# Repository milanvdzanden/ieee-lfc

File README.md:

# IEEE Line Follower Competition
This repository will serve as the main source of all technical details related to the Line Follower Competition. This repository also contains all design files for the robot template kit, which will be made available for purchase as well. Some example code will be provided but you are completely free to change these design files, code and even the robot to get an edge over the other teams.

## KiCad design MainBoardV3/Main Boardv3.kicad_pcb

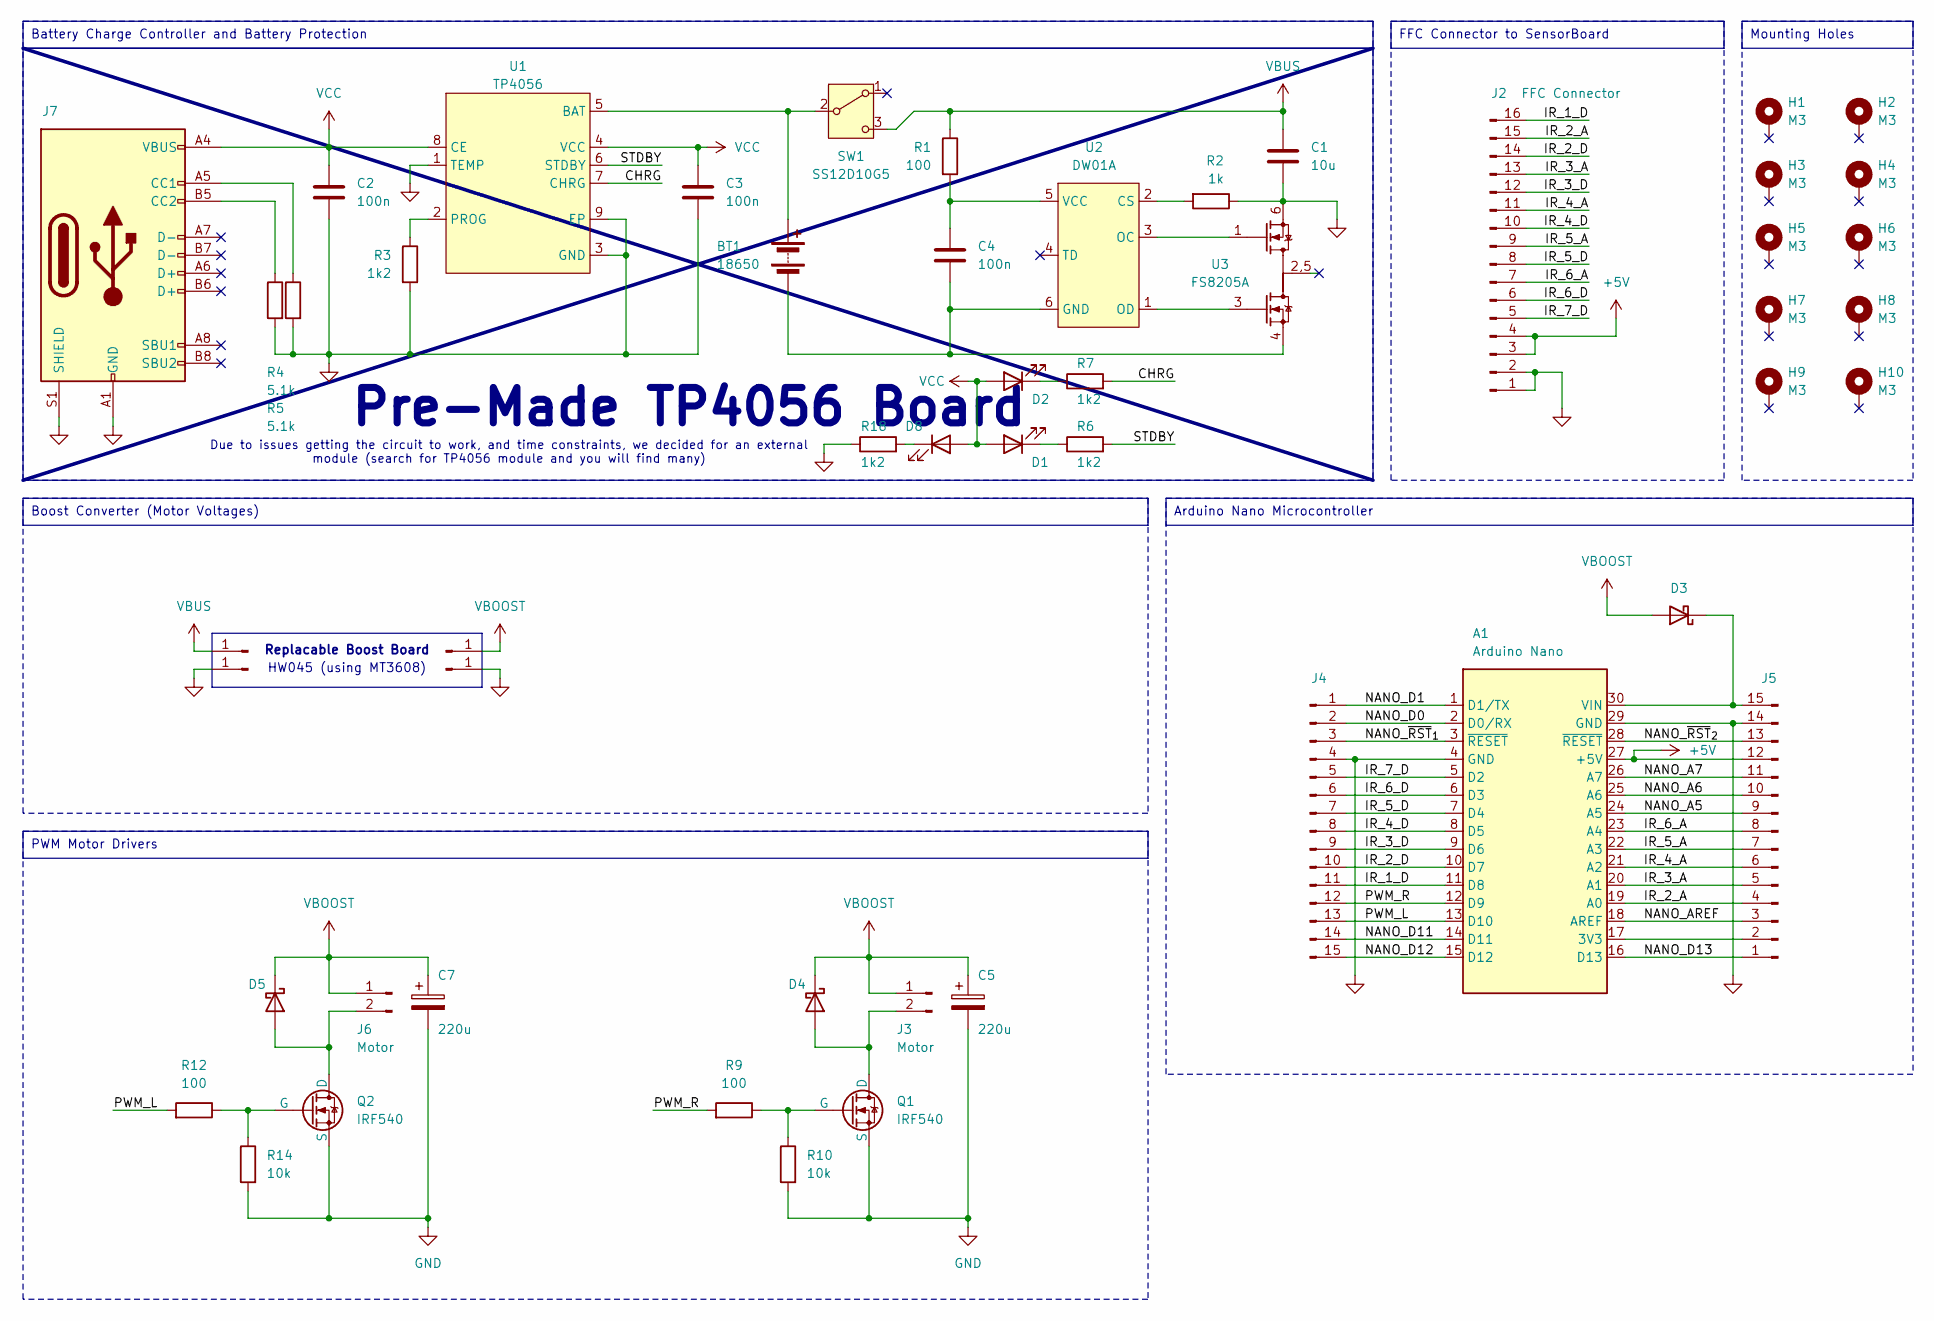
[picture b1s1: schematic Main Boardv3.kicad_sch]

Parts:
A1: Arduino Nano; Arduino_Nano
BT1: 18650; BatteryHolder_Keystone_1042_1x18650
C1: 10u; C_0603_1608Metric
C2, C3, C4: 100n; C_0603_1608Metric
C5, C7: 220u; CP_Radial_D8.0mm_P5.00mm
D1, D2, D8: LED; LED_0603_1608Metric
D3, D4, D5: D_Schottky; D_SMA
H1, H2, H3, H4, H5, H6, H7, H8, H9, H10: M3; MountingHole_Soldernut_M3
J2: FFC Connector; Hirose_FH12-16S-0.5SH_1x16-1MP_P0.50mm_Horizontal
J3, J6: Motor; TerminalBlock_bornier-2_P5.08mm
J4, J5: Row 2; PinSocket_1x15_P2.54mm_Vertical
J7: USB_C_Receptacle_USB2.0_16P; USB_C_Receptacle_GCT_USB4105-xx-A_16P_TopMnt_Horizontal
J101, J102, J103, J104: Conn_01x01_Pin; PinHeader_1x01_P2.54mm_Vertical
Q1, Q2: IRF540; TO-220F-3_Vertical
R1, R9, R12: 100; R_0603_1608Metric
R2: 1k; R_0603_1608Metric
R3, R6, R7, R18: 1k2; R_0603_1608Metric
R4, R5: 5.1k; R_0603_1608Metric
R10, R14: 10k; R_0603_1608Metric
SW1: SS12D10G5; SS12D10G5_SlideSwitch
U1: TP4056; Infineon_PG-DSO-8-27_3.9x4.9mm_EP2.65x3mm
U2: DW01A; SOT-23-6
U3: FS8205A; SOT-23-6

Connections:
+5V: A1.27 (+5V), J2.3, J2.4, J5.12
/CHRG: R7.2, U1.7 (CHRG)
/IR_1_D: A1.11 (D8), J2.16, J4.11
/IR_2_A: A1.19 (A0), J2.15, J5.4
/IR_2_D: A1.10 (D7), J2.14, J4.10
/IR_3_A: A1.20 (A1), J2.13, J5.5
/IR_3_D: A1.9 (D6), J2.12, J4.9
/IR_4_A: A1.21 (A2), J2.11, J5.6
/IR_4_D: A1.8 (D5), J2.10, J4.8
/IR_5_A: A1.22 (A3), J2.9, J5.7
/IR_5_D: A1.7 (D4), J2.8, J4.7
/IR_6_A: A1.23 (A4), J2.7, J5.8
/IR_6_D: A1.6 (D3), J2.6, J4.6
/IR_7_D: A1.5 (D2), J2.5, J4.5
/NANO_A5: A1.24 (A5), J5.9
/NANO_A6: A1.25 (A6), J5.10
/NANO_A7: A1.26 (A7), J5.11
/NANO_AREF: A1.18 (AREF), J5.3
/NANO_D0: A1.2 (D0/RX), J4.2
/NANO_D1: A1.1 (D1/TX), J4.1
/NANO_D11: A1.14 (D11), J4.14
/NANO_D12: A1.15 (D12), J4.15
/NANO_D13: A1.16 (D13), J5.1
/NANO_~RST_{1}: A1.3 (~RESET), J4.3
/NANO_~RST_{2}: A1.28 (~RESET), J5.13
/PWM_L: A1.13 (D10), J4.13, R12.2
/PWM_R: A1.12 (D9), J4.12, R9.2
/STDBY: R6.2, U1.6 (STDBY)
GND: A1.4 (GND), A1.29 (GND), C1.2, C2.2, C3.2, C5.2, C7.2, J2.1, J2.2, J4.4, J5.14, J7.A1 (GND), J7.A12 (GND), J7.B1 (GND), J7.B12 (GND), J7.S1 (SHIELD), J102.1, J104.1, Q1.3 (S), Q2.3 (S), R2.1, R3.2, R4.2, R5.2, R10.2, R14.2, R18.1, U1.1 (TEMP), U1.3 (GND), U1.9 (EP), U3.6
unnamed: A1.17 (3V3), J5.2
unnamed: A1.30 (VIN), D3.1 (K), J5.15
unnamed: BT1.1 (+), SW1.2 (B), U1.5 (BAT)
unnamed: BT1.2 (-), C4.2, U2.6 (GND), U3.4
unnamed: D1.1 (K), R6.1
unnamed: D2.1 (K), R7.1
unnamed: D4.2 (A), J3.2, Q1.2 (D)
unnamed: D5.2 (A), J6.2, Q2.2 (D)
unnamed: D8.1 (K), R18.2
unnamed: J7.A5 (CC1), R5.1
unnamed: J7.B5 (CC2), R4.1
unnamed: Q1.1 (G), R9.1, R10.1
unnamed: Q2.1 (G), R12.1, R14.1
unnamed: R3.1, U1.2 (PROG)
unnamed: R2.2, U2.2 (CS)
unnamed: U2.3 (OC), U3.1
unnamed: U2.1 (OD), U3.3
unnamed: C4.1, R1.2, U2.5 (VCC)
VBOOST: C5.1, C7.1, D3.2 (A), D4.1 (K), D5.1 (K), J3.1, J6.1, J103.1
VBUS: C1.1, J101.1, R1.1, SW1.3 (C)
VCC: C2.1, C3.1, D1.2 (A), D2.2 (A), D8.2 (A), J7.A4 (VBUS), J7.A9 (VBUS), J7.B4 (VBUS), J7.B9 (VBUS), U1.4 (VCC), U1.8 (CE)

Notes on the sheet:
Mounting Holes
Arduino Nano Microcontroller
Battery Charge Controller and Battery Protection
FFC Connector to SensorBoard
Boost Converter (Motor Voltages)
PWM Motor Drivers
HW045 (using MT3608)
Replacable Boost Board
Due to issues getting the circuit to work, and time constraints, we decided for an external module (search for TP4056 module and you will find many)
Pre-Made TP4056 Board

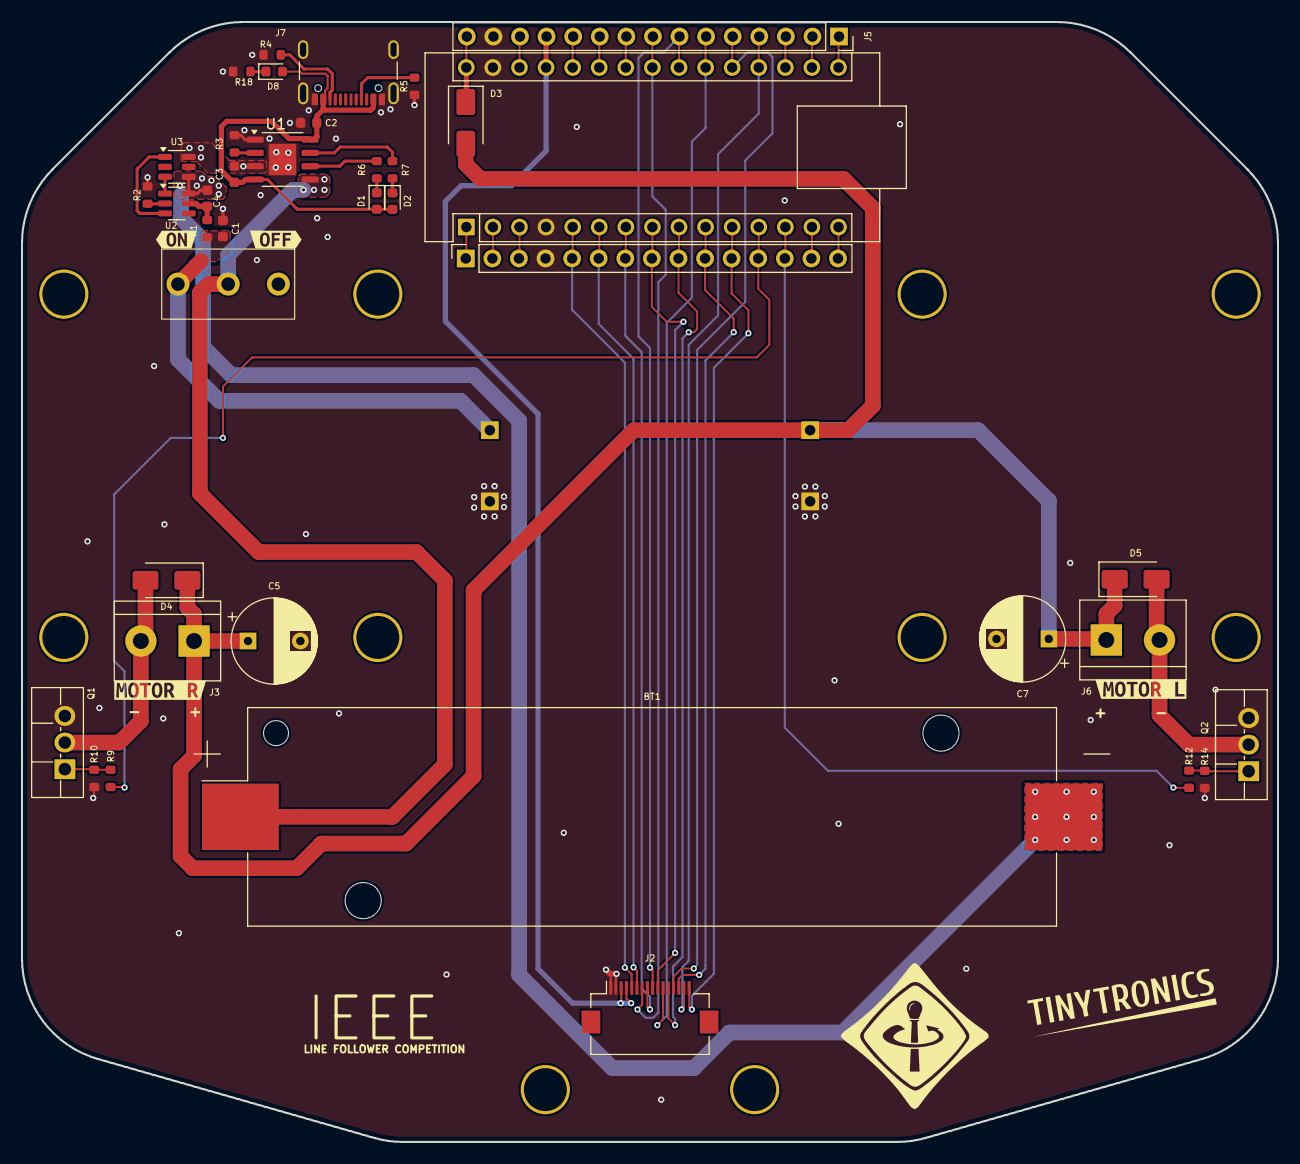
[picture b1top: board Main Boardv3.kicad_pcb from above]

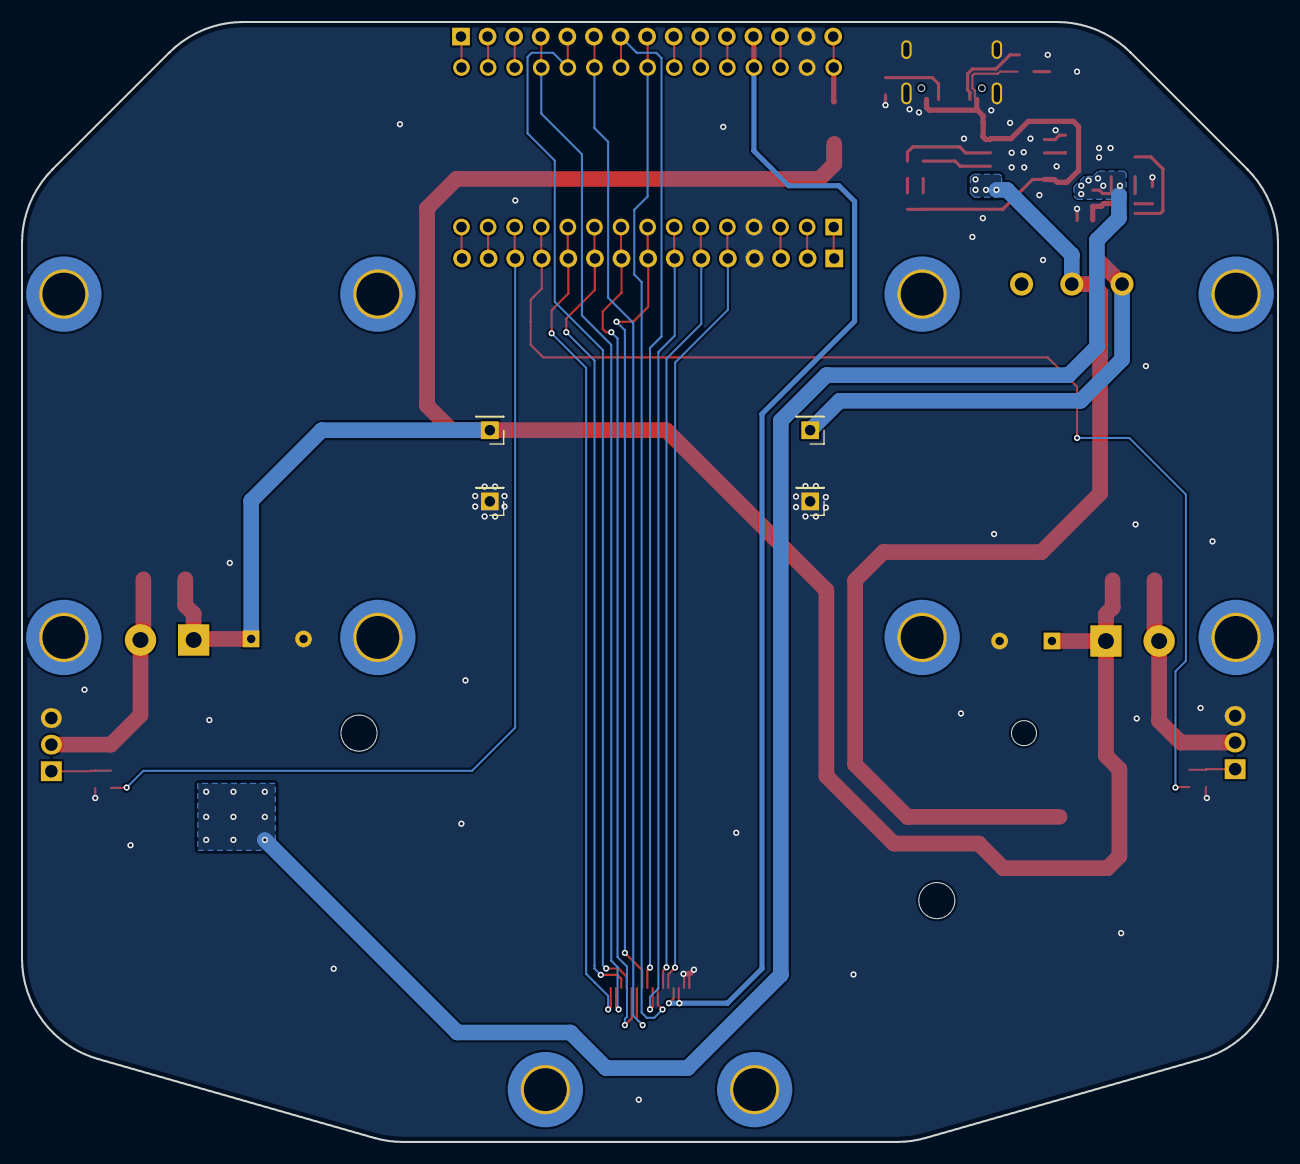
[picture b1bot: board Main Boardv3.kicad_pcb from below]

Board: 2 copper layers, 120.0 x 107.0 mm, 56 parts (14 on the bottom side), 50 nets.

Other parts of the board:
kibuzzard-666C7E6A: G***; kibuzzard-666C7E6A
kibuzzard-666C7E77: G***; kibuzzard-666C7E77
kibuzzard-666C76A4: G***; kibuzzard-666C76A4
kibuzzard-666C76B2: G***; kibuzzard-666C76B2

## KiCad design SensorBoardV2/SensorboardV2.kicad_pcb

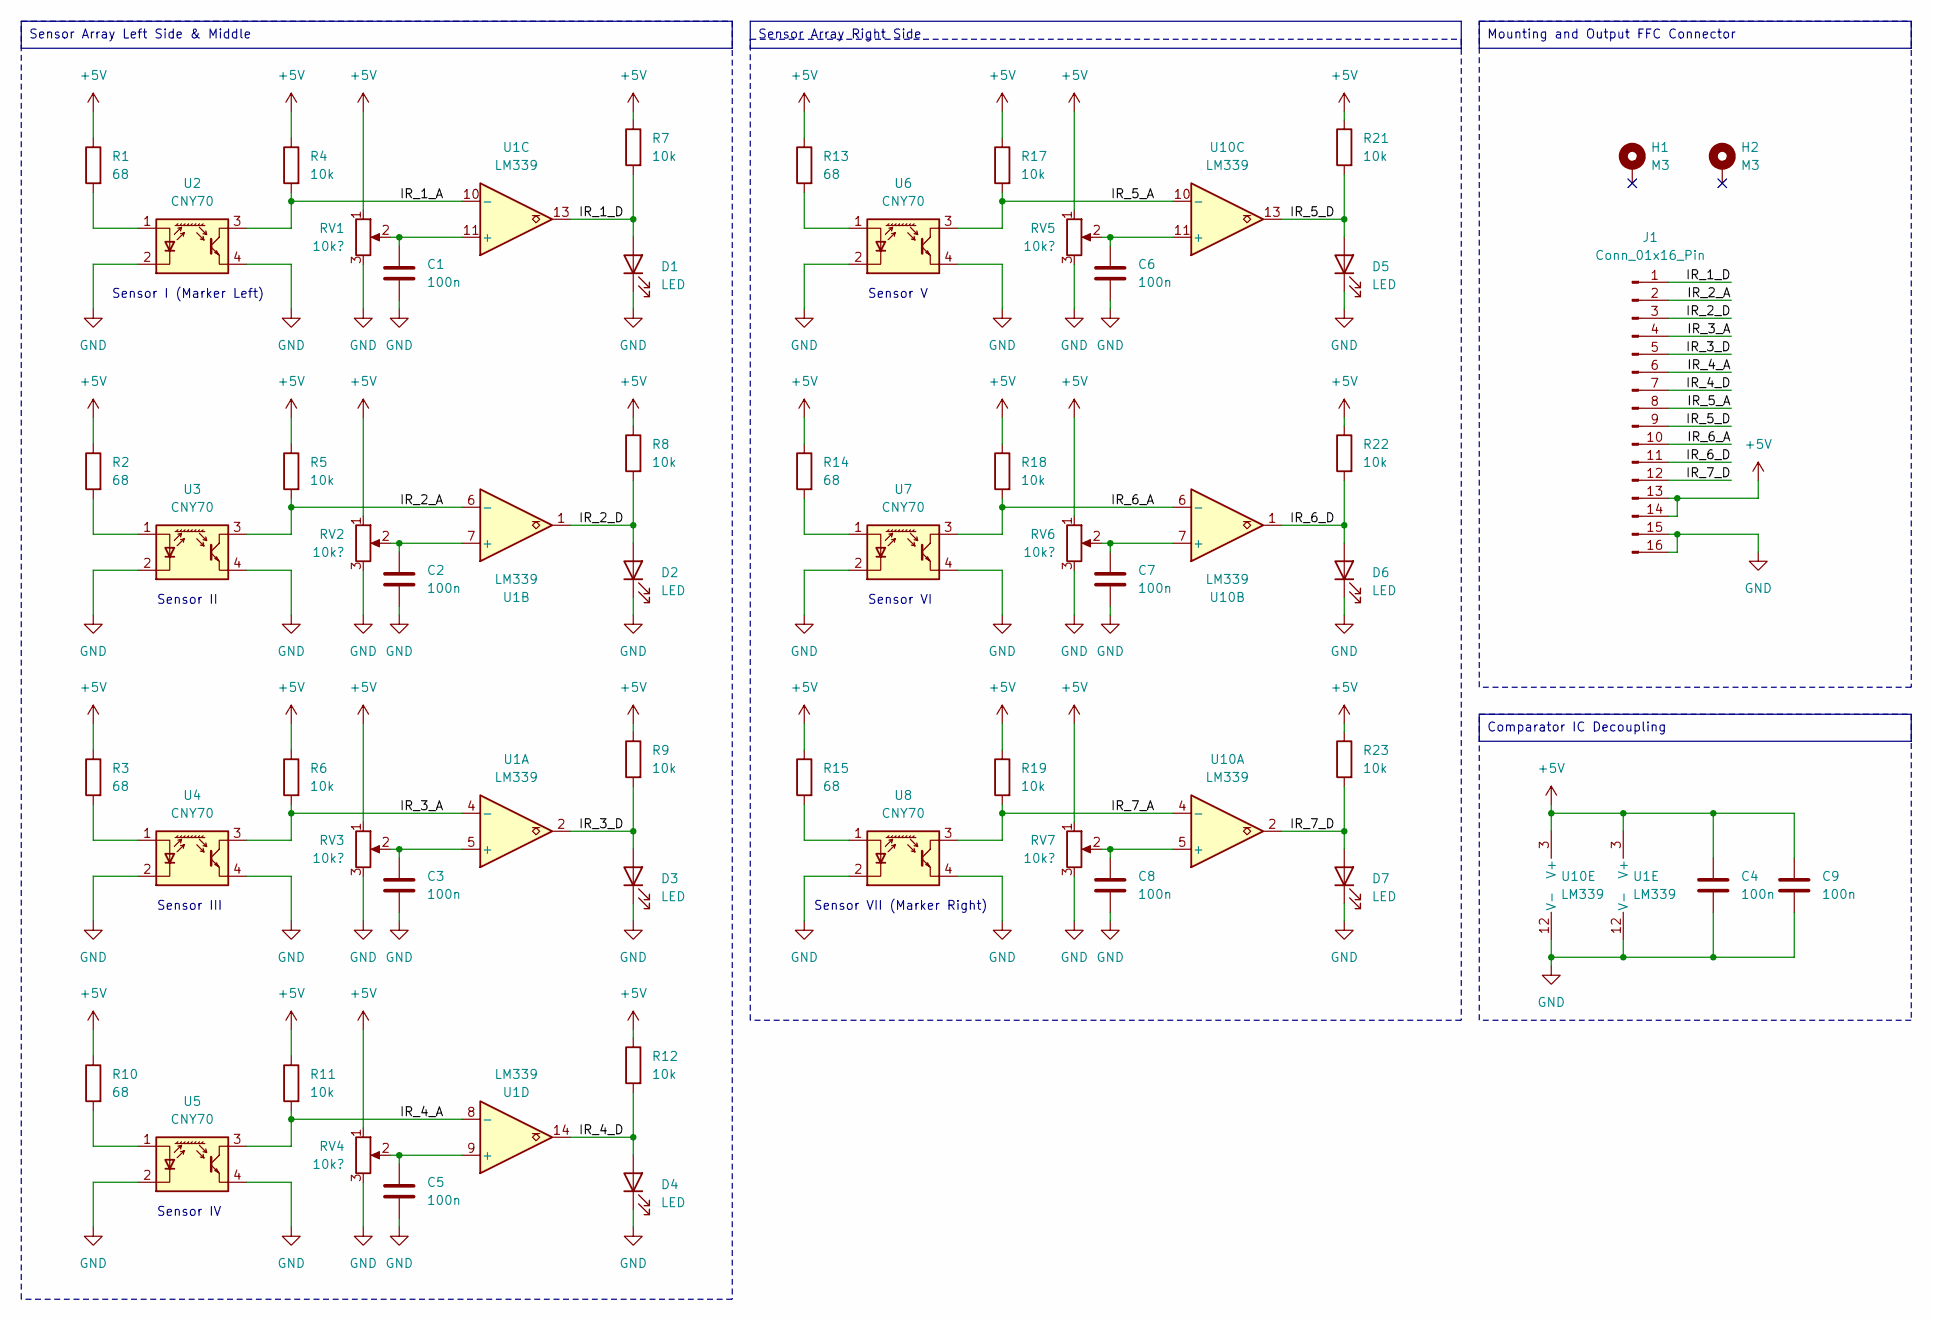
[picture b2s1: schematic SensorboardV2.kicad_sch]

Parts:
C1, C2, C3, C4, C5, C6, C7, C8, C9: 100n; C_0603_1608Metric
D1, D2, D3, D4, D5, D6, D7: LED; D_0603_1608Metric
H1, H2: M3; MountingHole_Soldernut_M3
J1: Conn_01x16_Pin; Hirose_FH12-16S-0.5SH_1x16-1MP_P0.50mm_Horizontal
R1, R2, R3, R10, R13, R14, R15: 68; R_0603_1608Metric
R4, R5, R6, R7, R8, R9, R11, R12, R17, R18, R19, R21, R22, R23: 10k; R_0603_1608Metric
RV1, RV2, RV3, RV4, RV5, RV6, RV7: 10k?; 3362P1222LF
U1, U10: LM339; SO-14_3.9x8.65mm_P1.27mm
U2, U3, U4, U5, U6, U7, U8: CNY70; Vishay_CNY70

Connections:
+5V: C4.1, C9.1, J1.13, J1.14, R1.1, R2.1, R3.1, R4.1, R5.1, R6.1, R7.1, R8.1, R9.1, R10.1, R11.1, R12.1, R13.1, R14.1, R15.1, R17.1, R18.1, R19.1, R21.1, R22.1, R23.1, RV1.1, RV2.1, RV3.1, RV4.1, RV5.1, RV6.1, RV7.1, U1.3 (V+), U10.3 (V+)
/IR_1_A: R4.2, U1.10 (-), U2.3 (C)
/IR_1_D: D1.2 (A), J1.1, R7.2, U1.13
/IR_2_A: J1.2, R5.2, U1.6 (-), U3.3 (C)
/IR_2_D: D2.2 (A), J1.3, R8.2, U1.1
/IR_3_A: J1.4, R6.2, U1.4 (-), U4.3 (C)
/IR_3_D: D3.2 (A), J1.5, R9.2, U1.2
/IR_4_A: J1.6, R11.2, U1.8 (-), U5.3 (C)
/IR_4_D: D4.2 (A), J1.7, R12.2, U1.14
/IR_5_A: J1.8, R17.2, U6.3 (C), U10.10 (-)
/IR_5_D: D5.2 (A), J1.9, R21.2, U10.13
/IR_6_A: J1.10, R18.2, U7.3 (C), U10.6 (-)
/IR_6_D: D6.2 (A), J1.11, R22.2, U10.1
/IR_7_A: R19.2, U8.3 (C), U10.4 (-)
/IR_7_D: D7.2 (A), J1.12, R23.2, U10.2
GND: C1.2, C2.2, C3.2, C4.2, C5.2, C6.2, C7.2, C8.2, C9.2, D1.1 (K), D2.1 (K), D3.1 (K), D4.1 (K), D5.1 (K), D6.1 (K), D7.1 (K), J1.15, J1.16, RV1.3, RV2.3, RV3.3, RV4.3, RV5.3, RV6.3, RV7.3, U1.12 (V-), U2.2 (K), U2.4 (E), U3.2 (K), U3.4 (E), U4.2 (K), U4.4 (E), U5.2 (K), U5.4 (E), U6.2 (K), U6.4 (E), U7.2 (K), U7.4 (E), U8.2 (K), U8.4 (E), U10.12 (V-)
unnamed: C3.1, RV3.2, U1.5 (+)
unnamed: C2.1, RV2.2, U1.7 (+)
unnamed: C1.1, RV1.2, U1.11 (+)
unnamed: C5.1, RV4.2, U1.9 (+)
unnamed: R1.2, U2.1 (A)
unnamed: R2.2, U3.1 (A)
unnamed: R3.2, U4.1 (A)
unnamed: R10.2, U5.1 (A)
unnamed: R13.2, U6.1 (A)
unnamed: R14.2, U7.1 (A)
unnamed: R15.2, U8.1 (A)
unnamed: C8.1, RV7.2, U10.5 (+)
unnamed: C7.1, RV6.2, U10.7 (+)
unnamed: C6.1, RV5.2, U10.11 (+)

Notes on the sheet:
Mounting and Output FFC Connector
Sensor Array Right Side
Sensor Array Left Side & Middle
Comparator IC Decoupling
Sensor VI
Sensor II
Sensor III
Sensor V
Sensor IV
Sensor I (Marker Left)
Sensor VII (Marker Right)

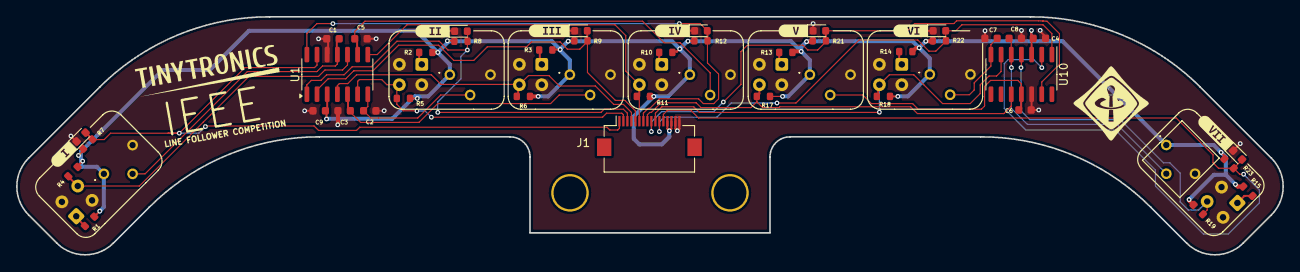
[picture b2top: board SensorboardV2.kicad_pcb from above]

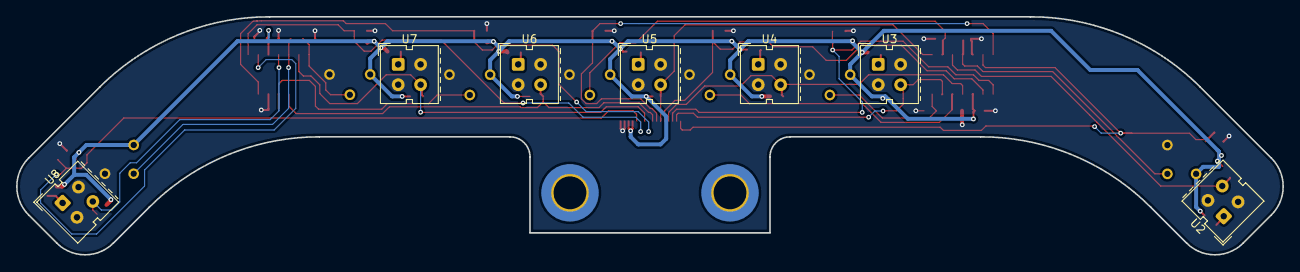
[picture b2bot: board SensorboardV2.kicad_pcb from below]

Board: 2 copper layers, 158.3 x 29.7 mm, 63 parts (9 on the bottom side), 30 nets.

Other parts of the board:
kibuzzard-6662E8B3: G***; kibuzzard-6662E8B3
kibuzzard-6662EBB8: G***; kibuzzard-6662EBB8
kibuzzard-6662EBDC: G***; kibuzzard-6662EBDC
kibuzzard-6662EBE3: G***; kibuzzard-6662EBE3
kibuzzard-6662EBED: G***; kibuzzard-6662EBED
kibuzzard-6662ED8C: G***; kibuzzard-6662ED8C
kibuzzard-6662ED27: G***; kibuzzard-6662ED27

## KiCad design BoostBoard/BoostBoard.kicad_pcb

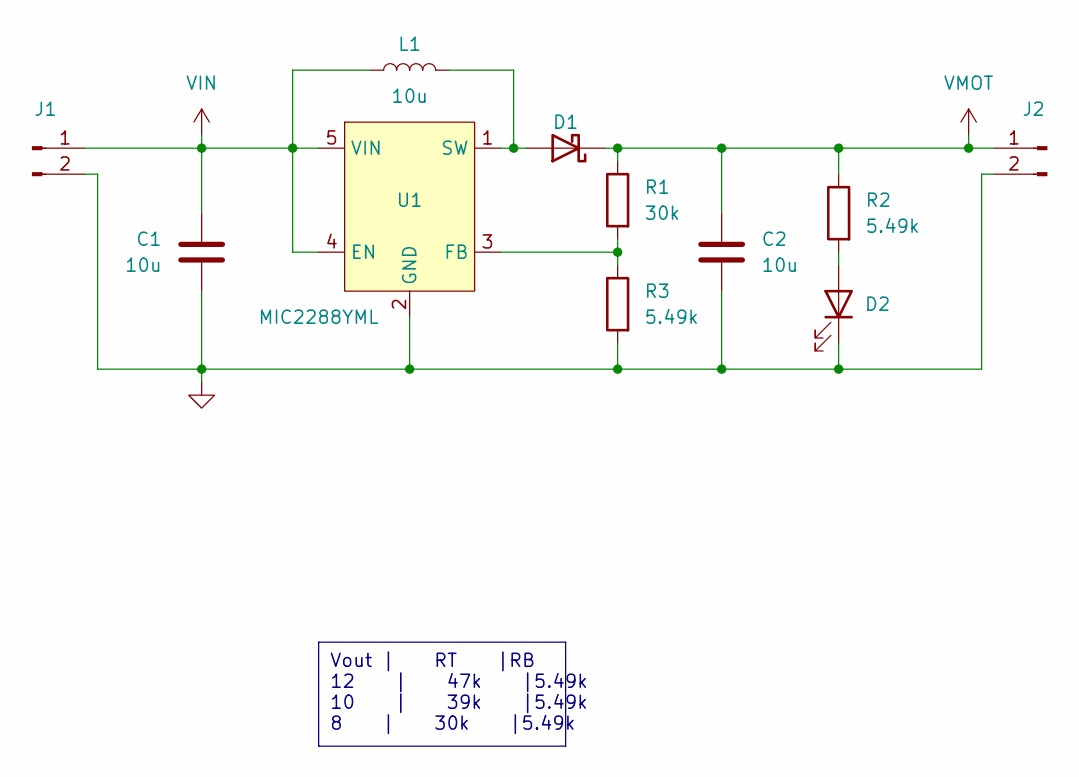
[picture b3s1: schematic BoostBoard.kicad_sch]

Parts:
C1, C2: 10u; C_0603_1608Metric
D1: D_Schottky; D_SMA
D2: LED; LED_0603_1608Metric
J1, J2: Conn_01x02_Pin; PinHeader_1x02_P2.54mm_Vertical
L1: 10u; Murata_LQH43xxx
R1: 30k; R_0603_1608Metric
R2, R3: 5.49k; R_0603_1608Metric
U1: MIC2288YML; SOT-23-5_HandSoldering

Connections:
GND: C1.2, C2.2, D2.1 (K), J1.2, J2.2, R3.2, U1.2 (GND)
unnamed: D1.2 (A), L1.2, U1.1 (SW)
unnamed: D2.2 (A), R2.2
unnamed: R1.2, R3.1, U1.3 (FB)
VIN: C1.1, J1.1, L1.1, U1.4 (EN), U1.5 (VIN)
VMOT: C2.1, D1.1 (K), J2.1, R1.1, R2.1

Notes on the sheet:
Vout | RT |RB 12 | 47k |5.49k 10 | 39k |5.49k 8 | 30k |5.49k

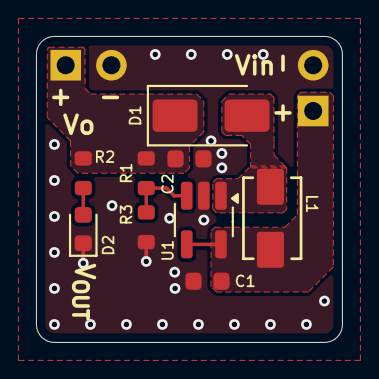
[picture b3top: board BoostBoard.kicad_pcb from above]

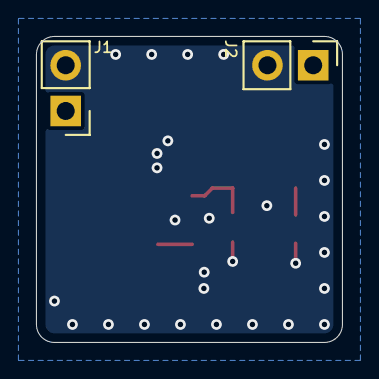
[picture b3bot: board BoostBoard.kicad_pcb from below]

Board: 2 copper layers, 17.0 x 17.0 mm, 11 parts (2 on the bottom side), 6 nets.

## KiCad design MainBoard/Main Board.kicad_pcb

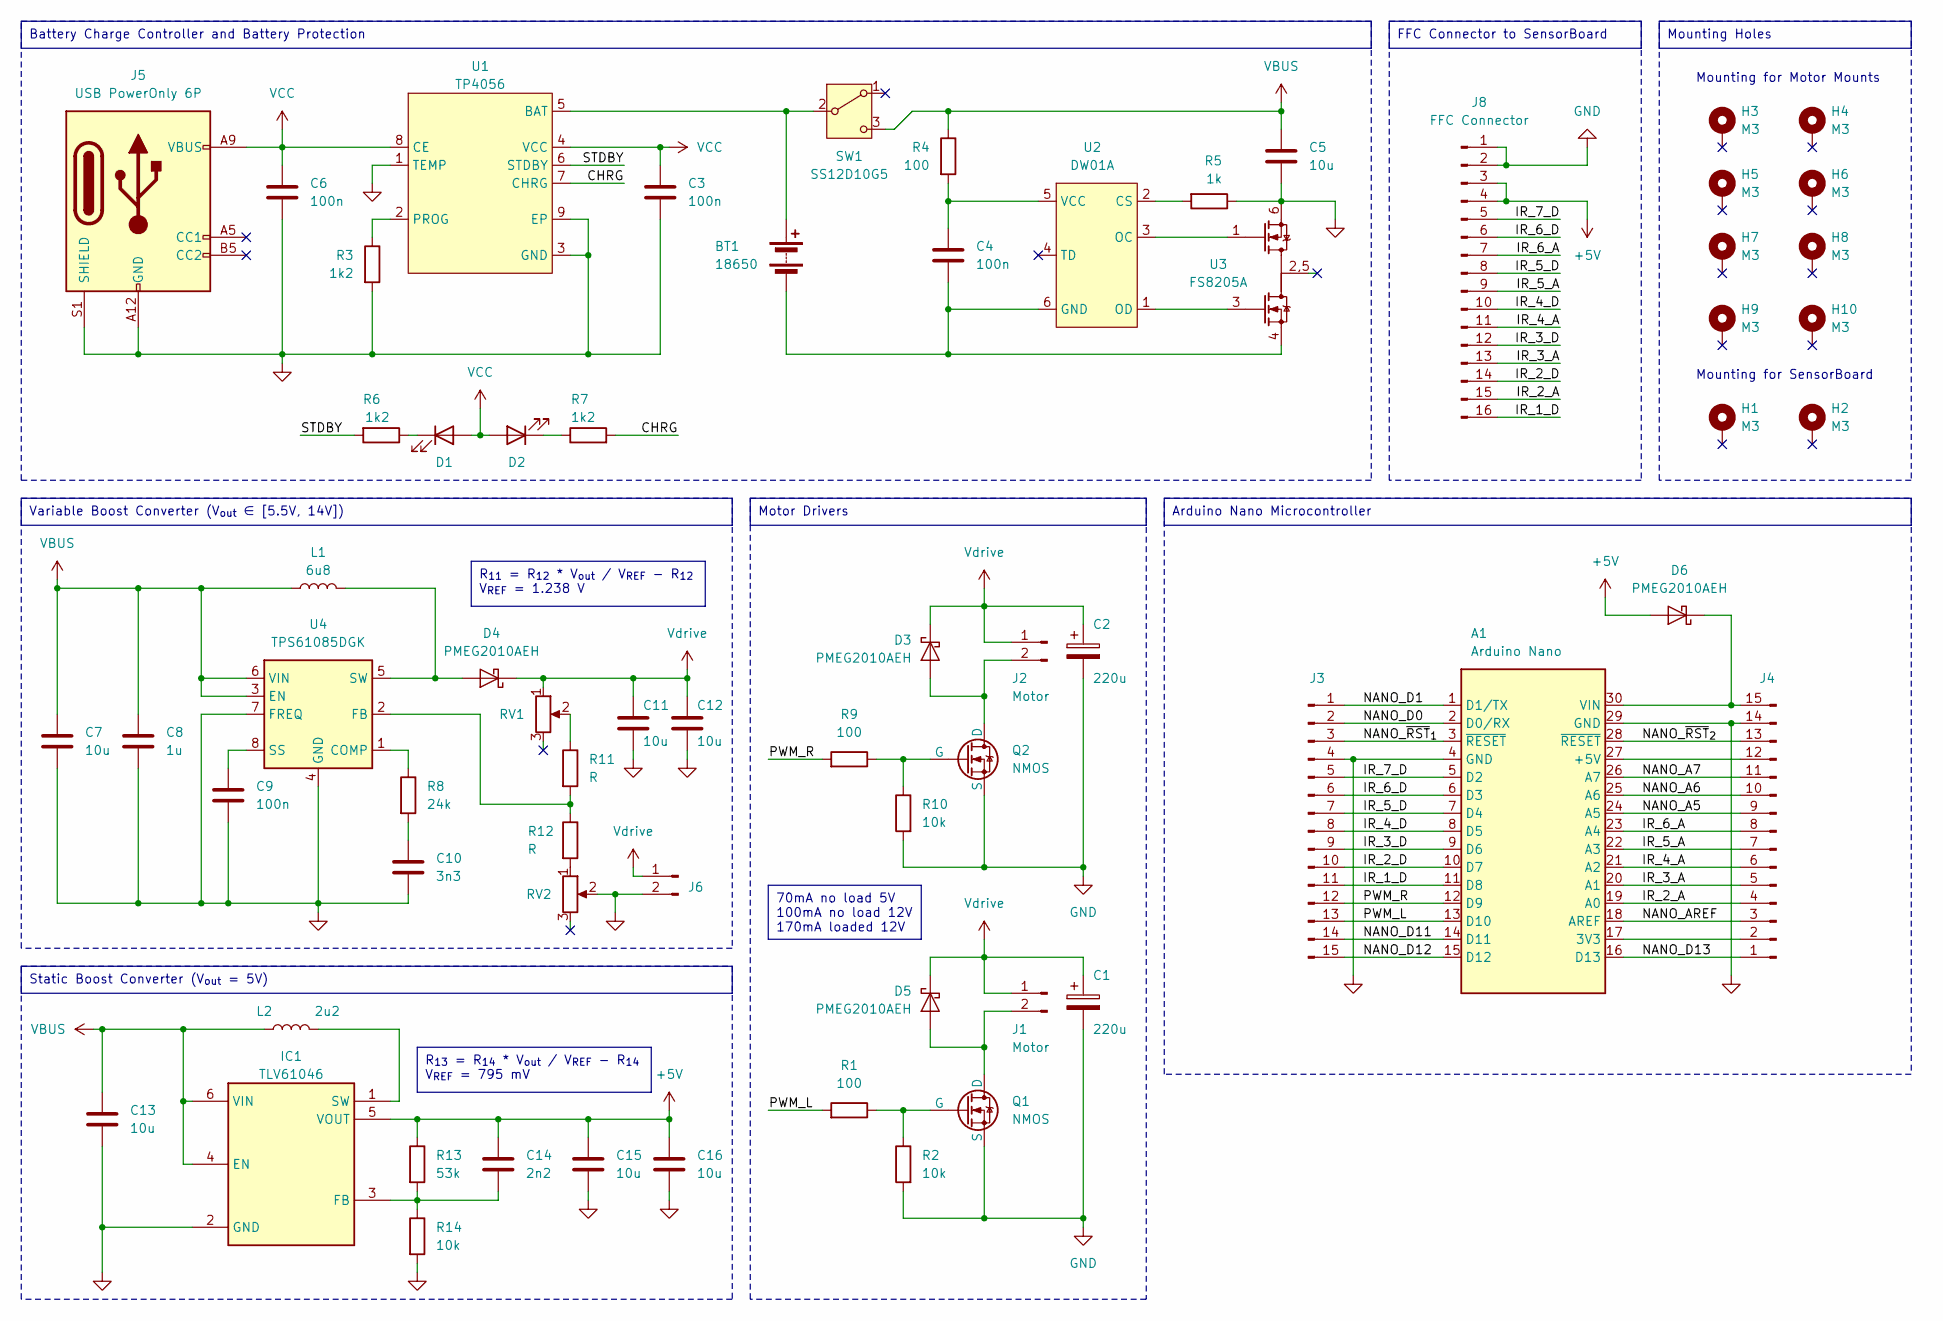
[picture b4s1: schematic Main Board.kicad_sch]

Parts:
A1: Arduino Nano; Arduino_Nano
BT1: 18650; BatteryHolder_Keystone_1042_1x18650
C1, C2: 220u; CP_Radial_D8.0mm_P5.00mm
C3, C4, C6, C9: 100n; C_0402_1005Metric
C5, C7, C11, C12, C13, C15, C16: 10u; C_0603_1608Metric
C8: 1u; C_0402_1005Metric
C10: 3n3; C_0402_1005Metric
C14: 2n2; C_0402_1005Metric
D1, D2: LED; LED_0603_1608Metric
D3, D4, D5, D6: PMEG2010AEH; D_SOD-123F
H1, H2, H3, H4, H5, H6, H7, H8, H9, H10: M3; MountingHole_Soldernut_M3
IC1: TLV61046; TLV61070ADBVR; Mouser Part Number 595-TLV61070ADBVR
J1, J2: Motor; TerminalBlock_bornier-2_P5.08mm
J3, J4: Row 2; PinSocket_1x15_P2.54mm_Vertical
J5: USB PowerOnly 6P; USB_C_Receptacle_GCT_USB4125-xx-x_6P_TopMnt_Horizontal
J6: Conn_01x02_Pin; PinHeader_1x02_P2.54mm_Vertical
J8: FFC Connector; Hirose_FH12-16S-0.5SH_1x16-1MP_P0.50mm_Horizontal
L1: 6u8; L_6.3x6.3_H3
L2: 2u2; L_Changjiang_FNR5030S
Q1, Q2: NMOS; TO-220F-3_Vertical
R1, R4, R9: 100; R_0402_1005Metric
R2, R10, R14: 10k; R_0402_1005Metric
R3, R6, R7: 1k2; R_0402_1005Metric
R5: 1k; R_0402_1005Metric
R8: 24k; R_0402_1005Metric
R11, R12: R; R_0402_1005Metric
R13: 53k; R_0402_1005Metric
RV1, RV2: R_Potentiometer; Potentiometer_Bourns_TC33X_Vertical
SW1: SS12D10G5; SS12D10G5_SlideSwitch
U1: TP4056; SO-8_3.9x4.9mm_P1.27mm
U2: DW01A; SOT-23-6
U3: FS8205A; SOT-23-6
U4: TPS61085DGK; VSSOP-8_3.0x3.0mm_P0.65mm

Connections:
+5V: C14.1, C15.1, C16.1, D6.2 (A), IC1.5 (VOUT), J8.3, J8.4, R13.1
/CHRG: R7.2, U1.7 (CHRG)
/IR_1_D: A1.11 (D8), J3.11, J8.16
/IR_2_A: A1.19 (A0), J4.4, J8.15
/IR_2_D: A1.10 (D7), J3.10, J8.14
/IR_3_A: A1.20 (A1), J4.5, J8.13
/IR_3_D: A1.9 (D6), J3.9, J8.12
/IR_4_A: A1.21 (A2), J4.6, J8.11
/IR_4_D: A1.8 (D5), J3.8, J8.10
/IR_5_A: A1.22 (A3), J4.7, J8.9
/IR_5_D: A1.7 (D4), J3.7, J8.8
/IR_6_A: A1.23 (A4), J4.8, J8.7
/IR_6_D: A1.6 (D3), J3.6, J8.6
/IR_7_D: A1.5 (D2), J3.5, J8.5
/NANO_A5: A1.24 (A5), J4.9
/NANO_A6: A1.25 (A6), J4.10
/NANO_A7: A1.26 (A7), J4.11
/NANO_AREF: A1.18 (AREF), J4.3
/NANO_D0: A1.2 (D0/RX), J3.2
/NANO_D1: A1.1 (D1/TX), J3.1
/NANO_D11: A1.14 (D11), J3.14
/NANO_D12: A1.15 (D12), J3.15
/NANO_D13: A1.16 (D13), J4.1
/NANO_~RST_{1}: A1.3 (~RESET), J3.3
/NANO_~RST_{2}: A1.28 (~RESET), J4.13
/PWM_L: A1.13 (D10), J3.13, R1.2
/PWM_R: A1.12 (D9), J3.12, R9.2
/STDBY: R6.2, U1.6 (STDBY)
GND: A1.4 (GND), A1.29 (GND), C1.2, C2.2, C3.2, C5.2, C6.2, C7.2, C8.2, C9.2, C10.2, C11.2, C12.2, C13.2, C15.2, C16.2, IC1.2 (GND), J3.4, J4.14, J5.A12 (GND), J5.B12 (GND), J5.S1 (SHIELD), J6.2, J8.1, J8.2, Q1.3 (S), Q2.3 (S), R2.2, R3.2, R5.1, R10.2, R14.2, RV2.2, U1.1 (TEMP), U1.3 (GND), U1.9 (EP), U3.6, U4.4 (GND), U4.7 (FREQ)
unnamed: A1.17 (3V3), J4.2
unnamed: A1.27 (+5V), J4.12
unnamed: A1.30 (VIN), D6.1 (K), J4.15
unnamed: BT1.1 (+), SW1.2 (B), U1.5 (BAT)
unnamed: BT1.2 (-), C4.2, U2.6 (GND), U3.4
unnamed: C10.1, R8.2
unnamed: D1.1 (K), R6.1
unnamed: D2.1 (K), R7.1
unnamed: D3.2 (A), J2.2, Q2.2 (D)
unnamed: D4.2 (A), L1.2, U4.5 (SW)
unnamed: D5.2 (A), J1.2, Q1.2 (D)
unnamed: C14.2, IC1.3 (FB), R13.2, R14.1
unnamed: IC1.1 (SW), L2.2
unnamed: Q1.1 (G), R1.1, R2.1
unnamed: Q2.1 (G), R9.1, R10.1
unnamed: R11.1, RV1.2
unnamed: R12.2, RV2.1
unnamed: R3.1, U1.2 (PROG)
unnamed: R5.2, U2.2 (CS)
unnamed: U2.3 (OC), U3.1
unnamed: U2.1 (OD), U3.3
unnamed: C4.1, R4.2, U2.5 (VCC)
unnamed: R8.1, U4.1 (COMP)
unnamed: R11.2, R12.1, U4.2 (FB)
unnamed: C9.1, U4.8 (SS)
VBUS: C5.1, C7.1, C8.1, C13.1, IC1.4 (EN), IC1.6 (VIN), L1.1, L2.1, R4.1, SW1.3 (C), U4.3 (EN), U4.6 (VIN)
VCC: C3.1, C6.1, D1.2 (A), D2.2 (A), J5.A9 (VBUS), J5.B9 (VBUS), U1.4 (VCC), U1.8 (CE)
Vdrive: C1.1, C2.1, C11.1, C12.1, D3.1 (K), D4.1 (K), D5.1 (K), J1.1, J2.1, J6.1, RV1.1

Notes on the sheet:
Mounting Holes
R_{11} = R_{12} * V_{out} / V_{REF} - R_{12} V_{REF} = 1.238 V
Arduino Nano Microcontroller
Battery Charge Controller and Battery Protection
FFC Connector to SensorBoard
Variable Boost Converter (V_{out} ∈ [5.5V, 14V])
70mA no load 5V 100mA no load 12V 170mA loaded 12V
Motor Drivers
R_{13} = R_{14} * V_{out} / V_{REF} - R_{14} V_{REF} = 795 mV
Static Boost Converter (V_{out} = 5V)
Mounting for SensorBoard
Mounting for Motor Mounts

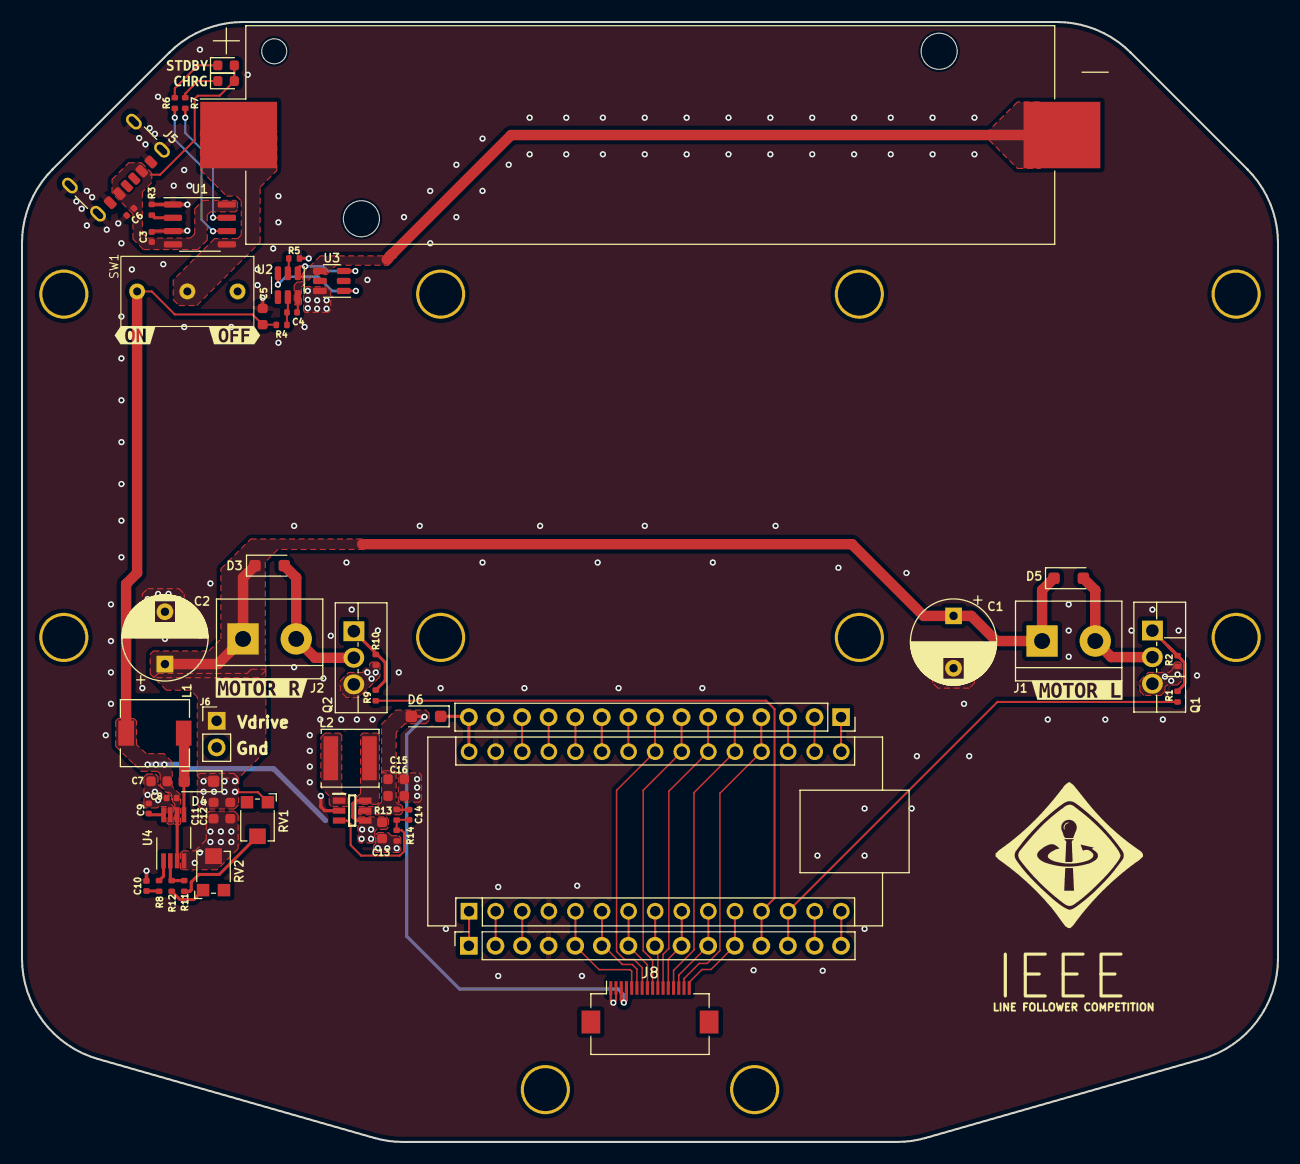
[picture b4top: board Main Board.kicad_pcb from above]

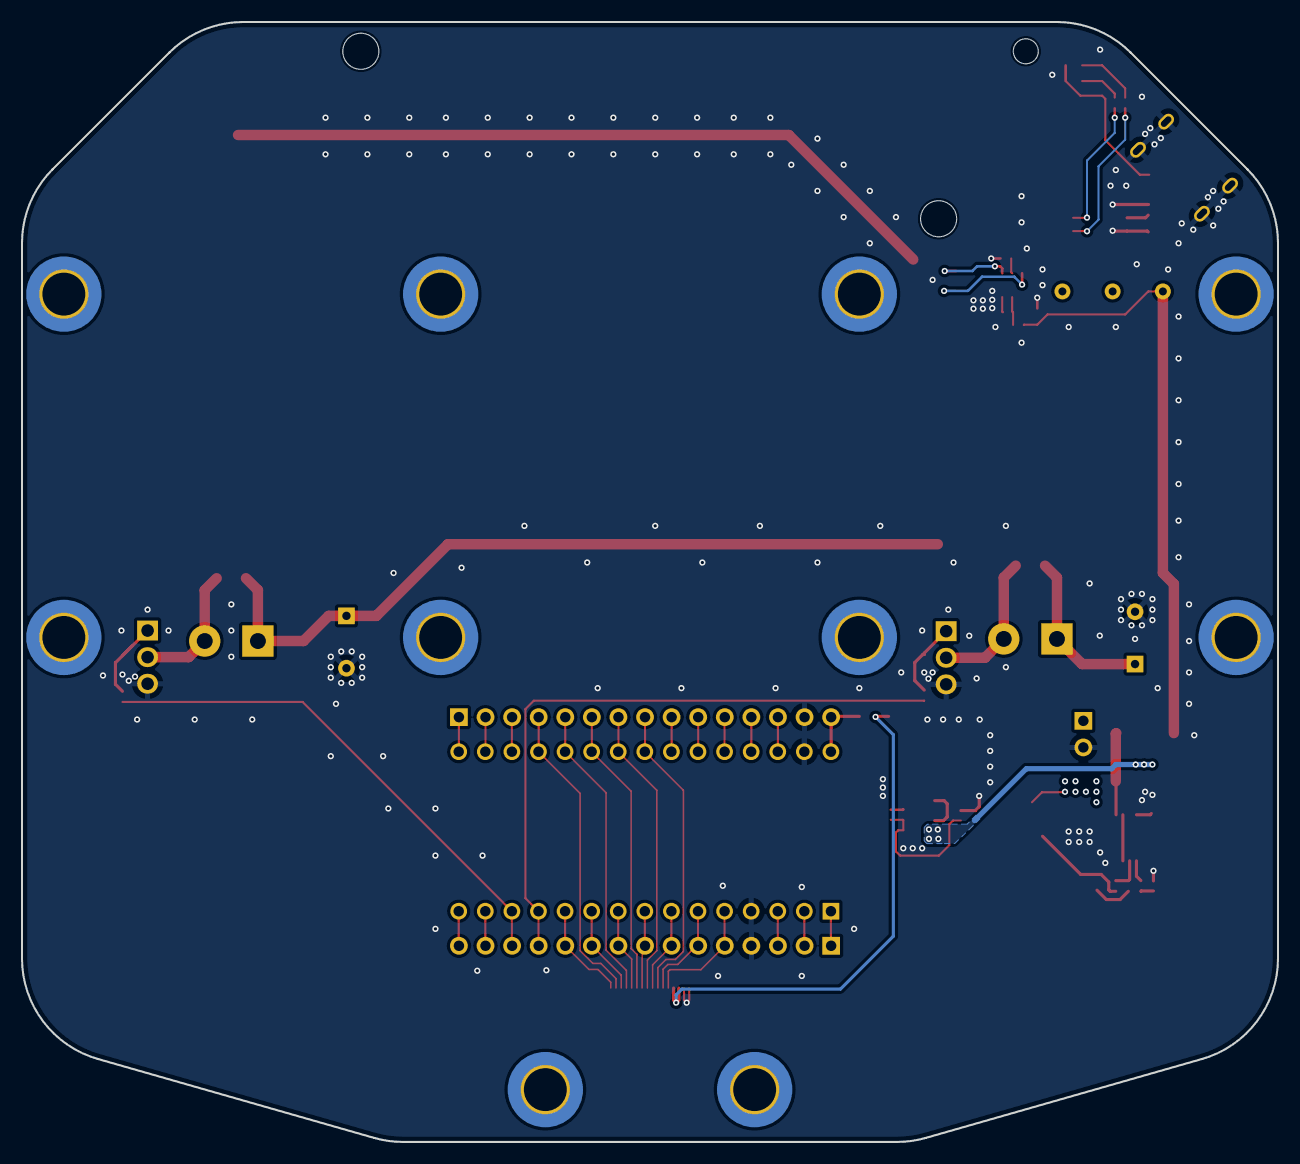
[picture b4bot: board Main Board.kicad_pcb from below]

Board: 2 copper layers, 120.0 x 107.0 mm, 73 parts (10 on the bottom side), 57 nets.

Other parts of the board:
kibuzzard-666C7E6A: G***; kibuzzard-666C7E6A
kibuzzard-666C7E77: G***; kibuzzard-666C7E77
kibuzzard-666C76A4: G***; kibuzzard-666C76A4
kibuzzard-666C76B2: G***; kibuzzard-666C76B2
kibuzzard-666C77C1: G***; kibuzzard-666C77C1
kibuzzard-666C77C8: G***; kibuzzard-666C77C8

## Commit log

2024-06-12 Up to date files
2024-06-12 Renamed some files
2024-06-12 Cleaned up MainBoard Schematic
2024-06-12 Small Changes to mainboard schematic
2024-06-12 SensorBoard Updates
2024-06-12 Removed backup files
2024-06-12 Removed backups
2024-06-12 Updated Mainboard
2024-06-12 Main board pcb traced
2024-06-12 Updated Version
2024-06-12 Version updated
2024-06-14 progressed on main board
    Made some more connections. Not fully finished it, but added it for completeness
2024-06-14 Finished MainBoard
2024-06-14 Removed unneccesary filed
2024-06-14 Pinout Update
2024-11-17 Created SensorboardV2
2024-11-23 Added boost board, updated schematic
2024-11-28 Uploaded Cad Models and recent PCB
2025-02-13 Final Update
